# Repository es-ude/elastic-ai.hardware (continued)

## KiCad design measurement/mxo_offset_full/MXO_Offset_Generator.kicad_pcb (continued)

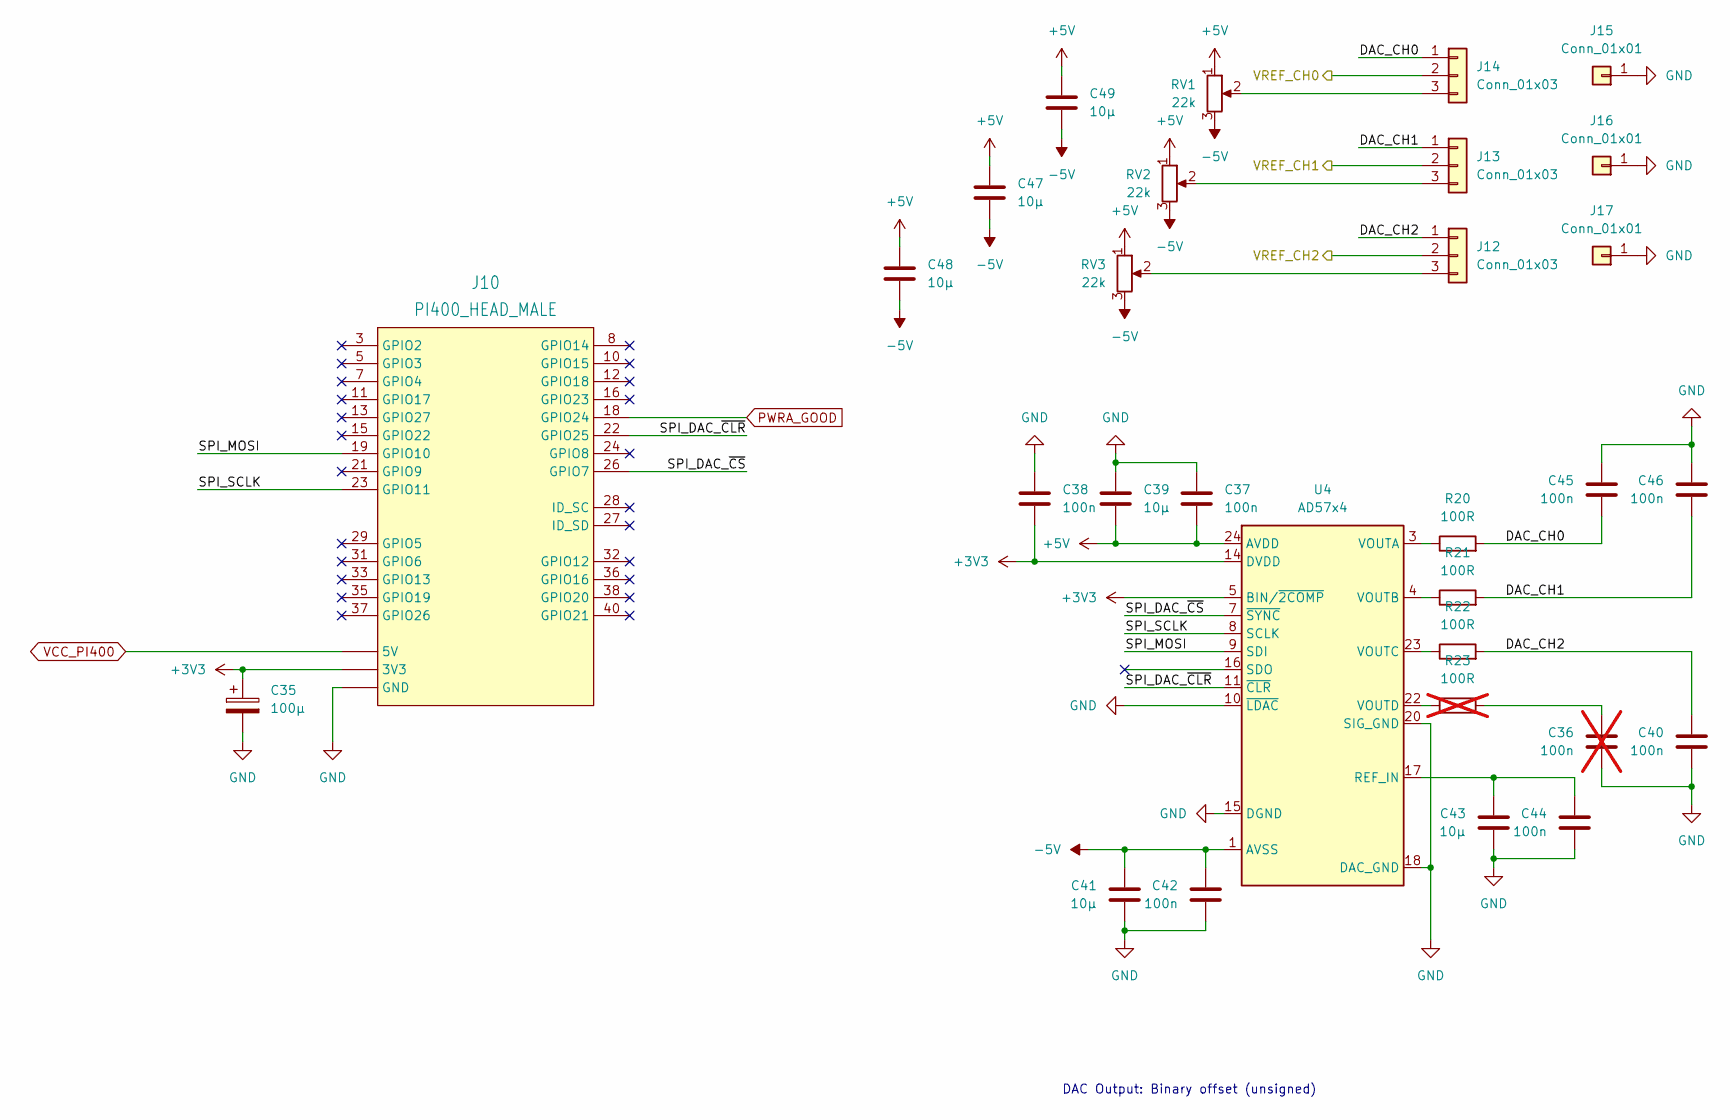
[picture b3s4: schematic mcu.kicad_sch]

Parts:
C35: 100µ; CP_Elec_4x3
C36: 100n; C_0603_1608Metric; not fitted
C37, C38, C40, C42, C44, C45, C46: 100n; C_0603_1608Metric
C39, C41, C43, C47, C48, C49: 10µ; C_0805_2012Metric
J10: PI400_HEAD_MALE; rpi400_header
J12, J13, J14: Conn_01x03; PinHeader_1x03_P2.54mm_Vertical
J15, J16, J17: Conn_01x01; PinHeader_1x01_P2.54mm_Vertical
R20, R21, R22: 100R; R_0603_1608Metric
R23: 100R; R_0603_1608Metric; not fitted
RV1, RV2, RV3: 22k; Potentiometer_Vishay_T73YP_Vertical
U4: AD57x4; TSSOP-24-1EP_4.4x7.8mm_P0.65mm_EP3.2x5mm

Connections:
+3V3: C35.1, C38.2, J10.1 (3V3), J10.17 (3V3), U4.5 (BIN/~2COMP), U4.14 (DVDD); also elsewhere on the board
+5V: C37.2, C39.2, C47.1, C48.1, C49.1, RV1.1, RV2.1, RV3.1, U4.24 (AVDD); also elsewhere on the board
-5V: C41.1, C42.1, C47.2, C48.2, C49.2, RV1.3, RV2.3, RV3.3, U4.1 (AVSS), U4.25 (AVSS_EXP); also elsewhere on the board
/Control-Unit/DAC_CH0: C45.2, J14.1, R20.2
/Control-Unit/DAC_CH1: C46.2, J13.1, R21.2
/Control-Unit/DAC_CH2: C40.1, J12.1, R22.2
/Control-Unit/SPI_DAC_~CLR: J10.22 (GPIO25), U4.11 (~CLR)
/Control-Unit/SPI_DAC_~CS: J10.26 (GPIO7), U4.7 (~SYNC)
/Control-Unit/SPI_MOSI: J10.19 (GPIO10), U4.9 (SDI)
/Control-Unit/SPI_SCLK: J10.23 (GPIO11), U4.8 (SCLK)
/Control-Unit/VREF_CH0: J14.2; also elsewhere on the board
/Control-Unit/VREF_CH1: J13.2; also elsewhere on the board
/Control-Unit/VREF_CH2: J12.2; also elsewhere on the board
GND: C35.2, C36.2, C37.1, C38.1, C39.1, C40.2, C41.2, C42.2, C43.2, C44.2, C45.1, C46.1, J10.6 (GND), J10.9 (GND), J10.14 (GND), J10.20 (GND), J10.25 (GND), J10.30 (GND), J10.34 (GND), J10.39 (GND), J15.1, J16.1, J17.1, U4.10 (~LDAC), U4.15 (DGND), U4.18 (DAC_GND), U4.19 (DAC_GND), U4.20 (SIG_GND), U4.21 (SIG_GND); also elsewhere on the board
unnamed: C36.1, R23.2
unnamed: J12.3, RV3.2
unnamed: J13.3, RV2.2
unnamed: J14.3, RV1.2
unnamed: C43.1, C44.1, U4.17 (REF_IN)
unnamed: R20.1, U4.3 (VOUTA)
unnamed: R21.1, U4.4 (VOUTB)
unnamed: R22.1, U4.23 (VOUTC)
unnamed: R23.1, U4.22 (VOUTD)
PWRA_GOOD: J10.18 (GPIO24); also elsewhere on the board
VCC_PI400: J10.2 (5V), J10.4 (5V); also elsewhere on the board

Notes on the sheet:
DAC Output: Binary offset (unsigned)

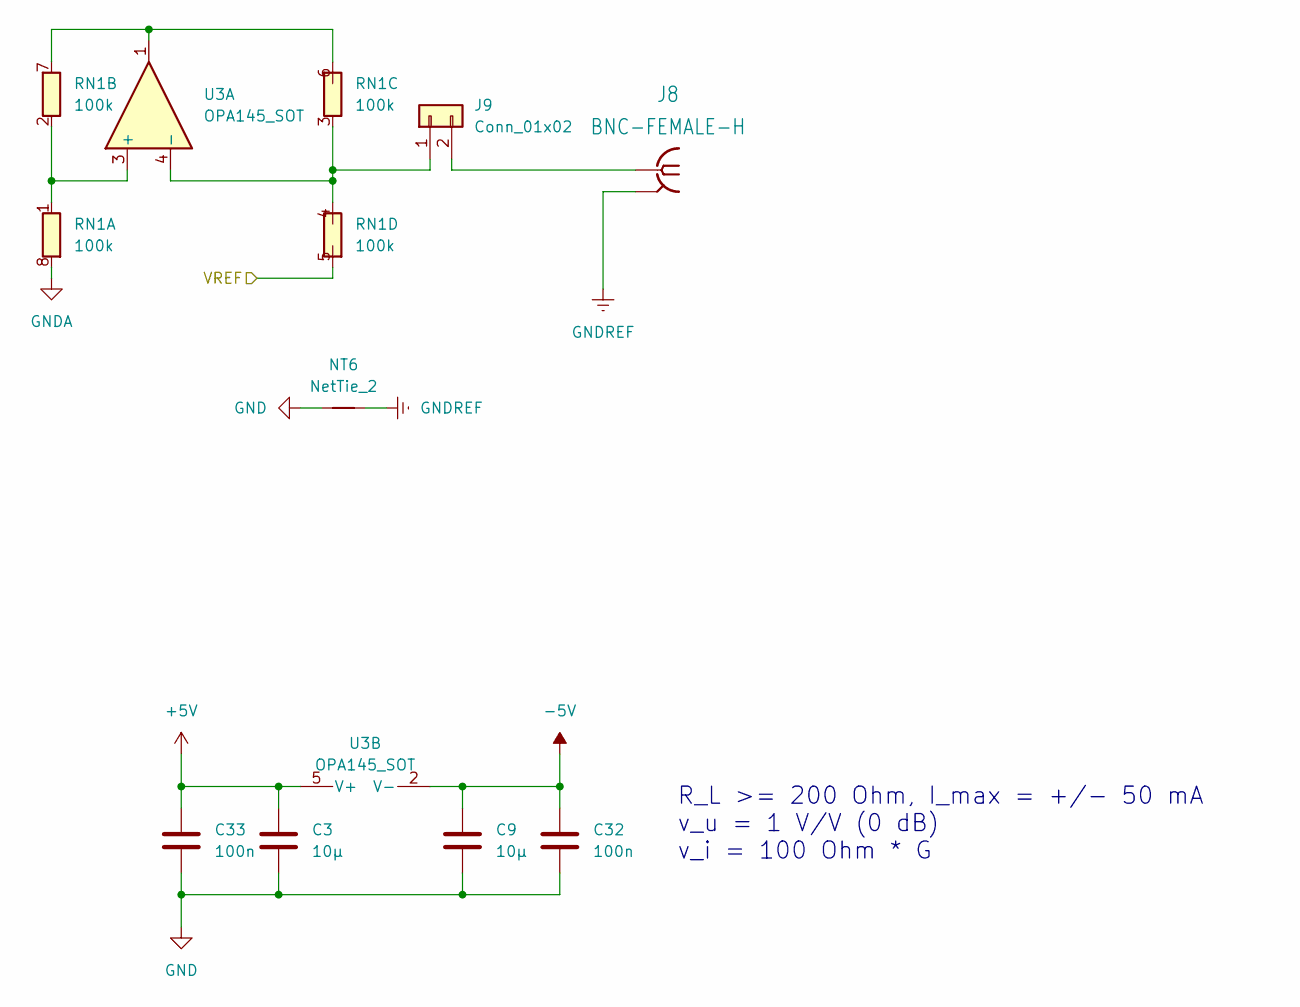
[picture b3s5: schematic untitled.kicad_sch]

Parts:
C3, C9: 10µ; C_0805_2012Metric
C32, C33: 100n; C_0603_1608Metric
J8: BNC-FEMALE-H; BNC-MALE-H
J9: Conn_01x02; PinHeader_1x02_P2.54mm_Vertical
NT6: NetTie_2; NetTie-2_SMD_Pad0.5mm
RN1: 100k; RESCAXE80P320X160X70-8N
U3: OPA145_SOT; SOT-23-5_HandSoldering

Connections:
+5V: C3.1, C33.1, U3.5 (V+); also elsewhere on the board
-5V: C9.1, C32.1, U3.2 (V-); also elsewhere on the board
/Control-Unit/VREF_CH2: RN1.5 (R4.2); also elsewhere on the board
GND: C3.2, C9.2, C32.2, C33.2, NT6.1; also elsewhere on the board
GNDA: RN1.8 (R1.2)
GNDREF: J8.2 (GND), NT6.2; also elsewhere on the board
unnamed: J8.1 (SIG), J9.2
unnamed: J9.1, RN1.3 (R3.1), RN1.4 (R4.1), U3.4 (-)
unnamed: RN1.1 (R1.1), RN1.2 (R2.1), U3.3 (+)
unnamed: RN1.6 (R3.2), RN1.7 (R2.2), U3.1

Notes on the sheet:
R_L >= 200 Ohm, I_max = +/- 50 mA v_u = 1 V/V (0 dB) v_i = 100 Ohm * G

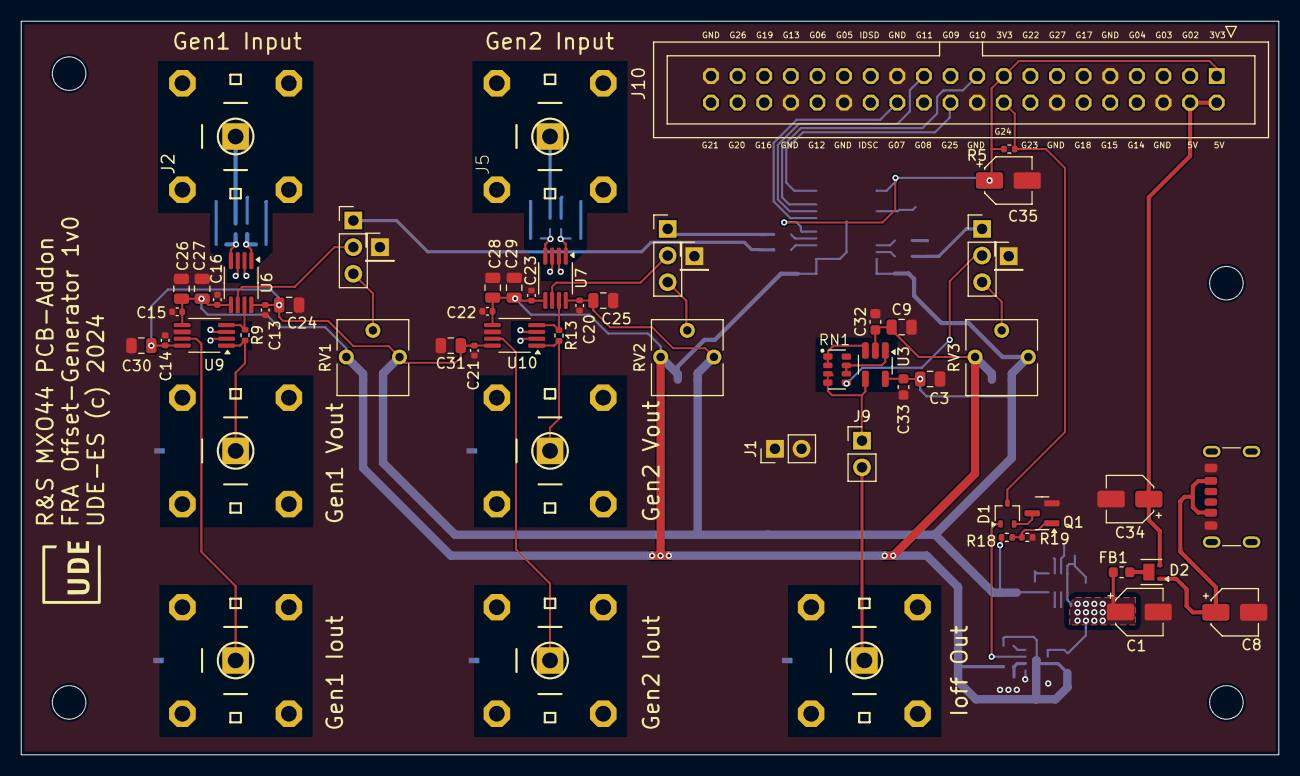
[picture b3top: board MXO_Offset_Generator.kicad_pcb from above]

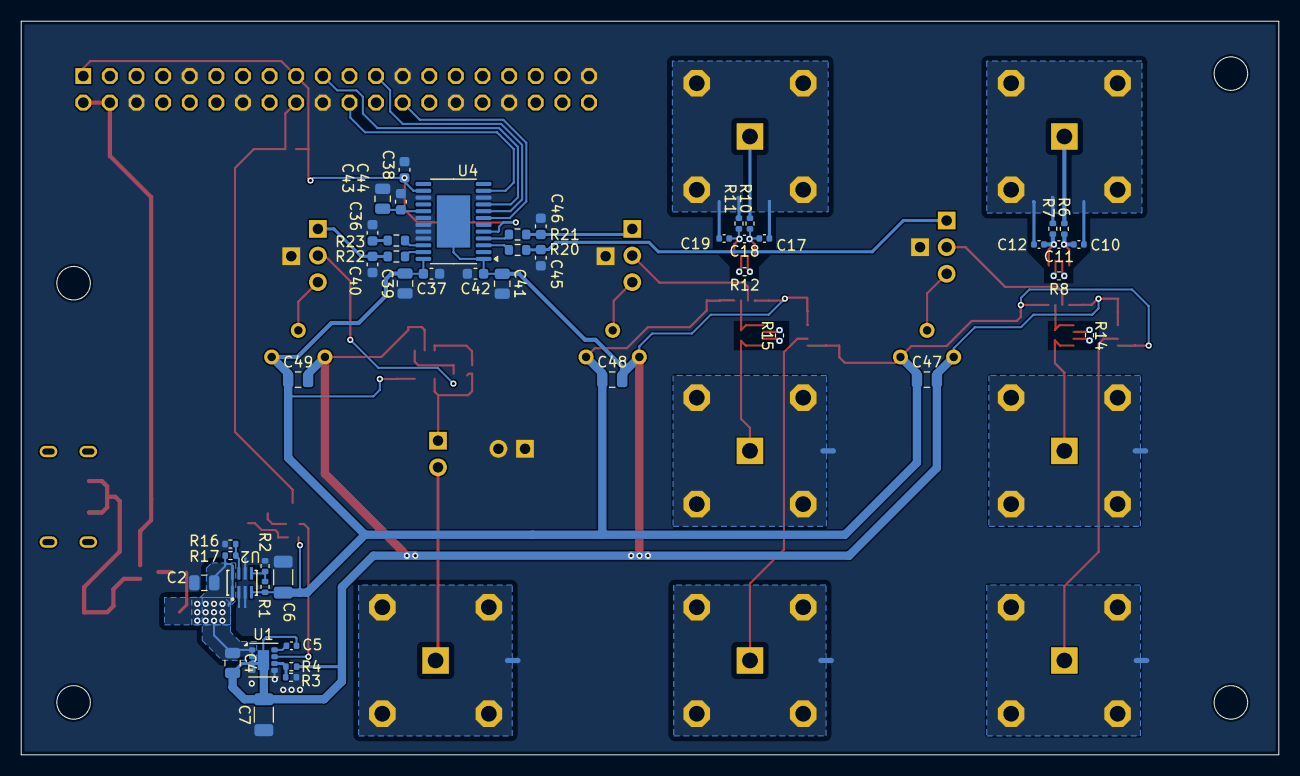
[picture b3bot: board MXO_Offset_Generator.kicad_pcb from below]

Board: 2 copper layers, 120.0 x 70.0 mm, 114 parts (51 on the bottom side), 60 nets.

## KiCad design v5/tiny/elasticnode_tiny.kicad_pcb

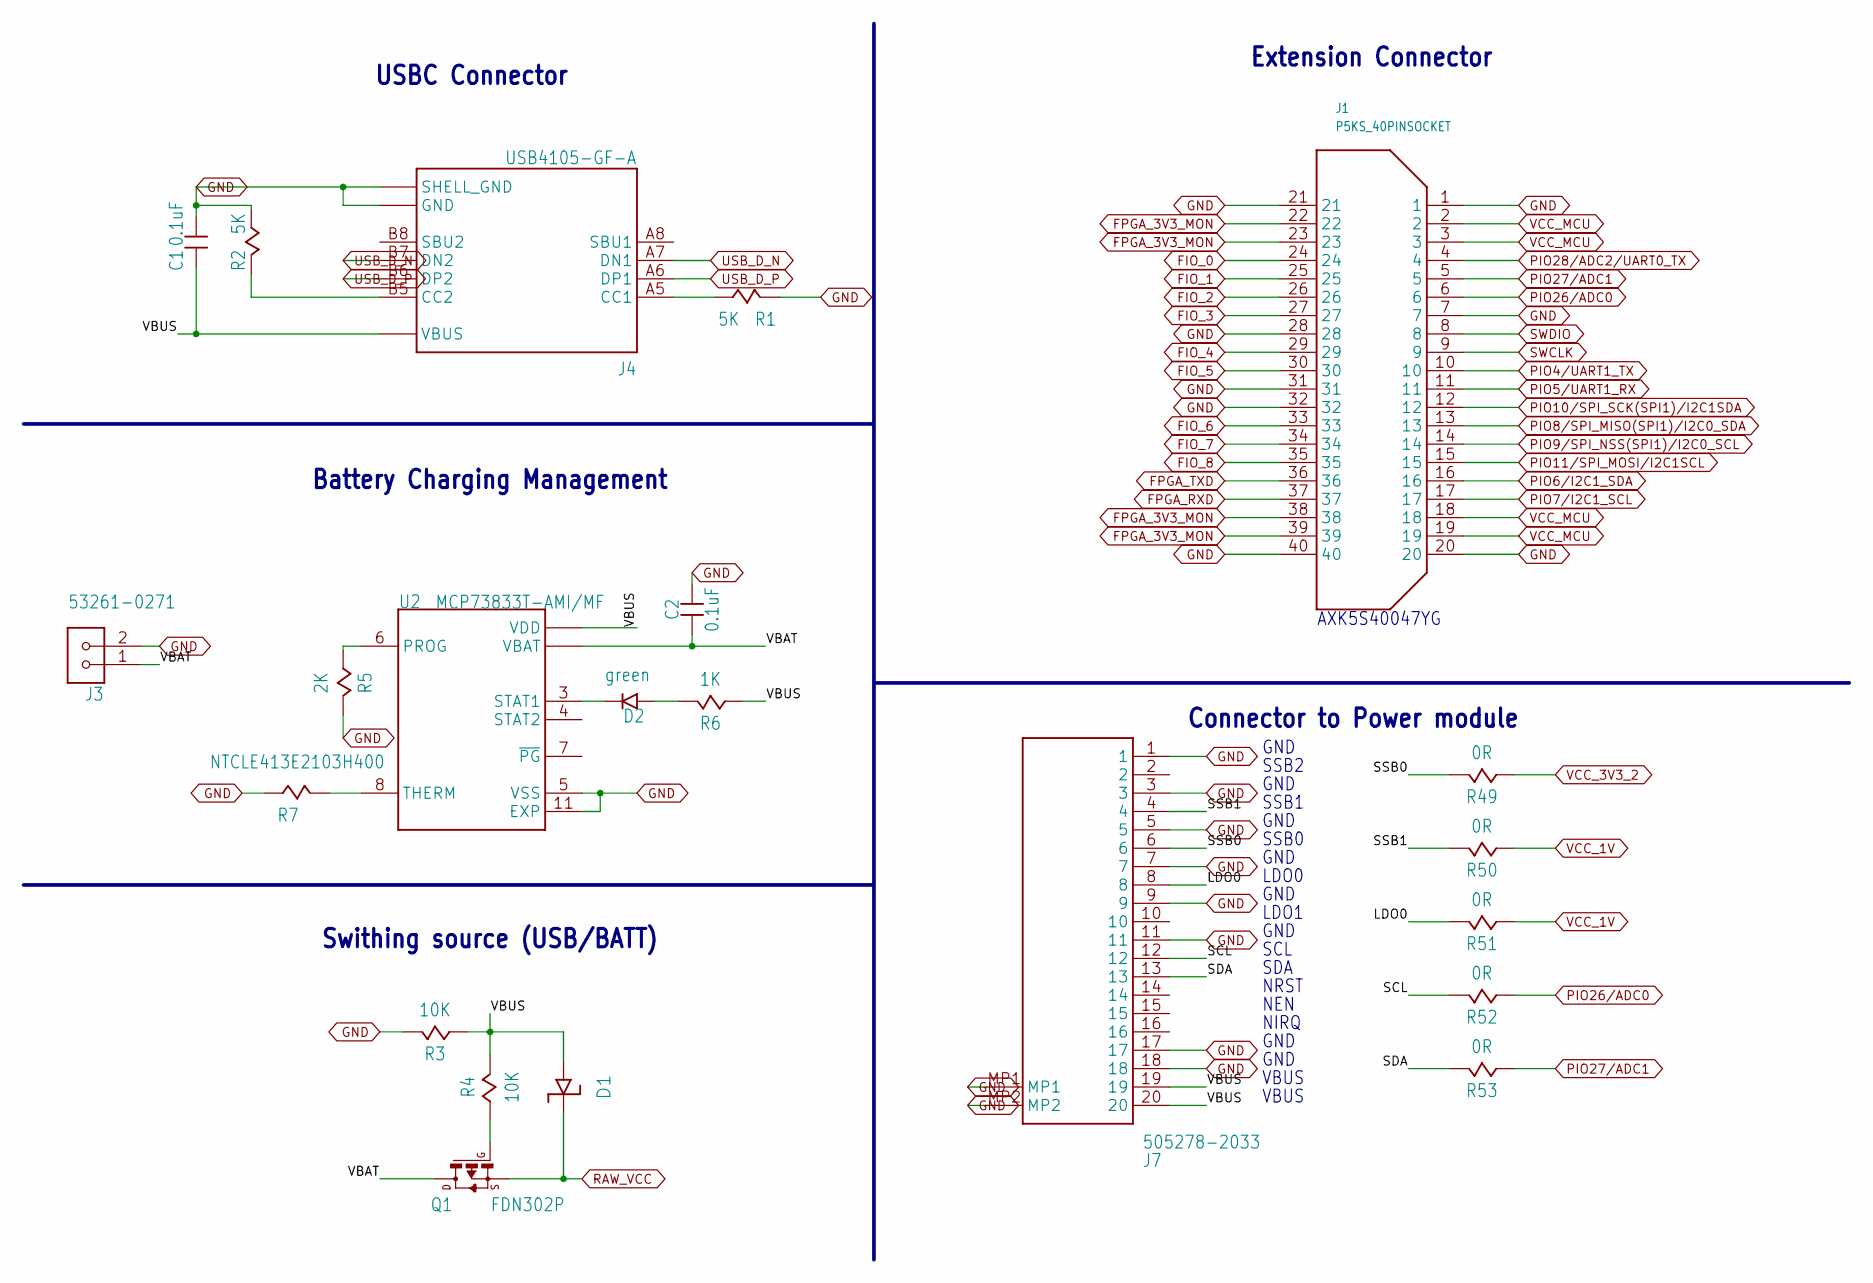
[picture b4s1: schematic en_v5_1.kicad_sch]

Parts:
C1: 0.1uF; 0402
C2: 0.1uF; 0805
D1: DIODEB5817W; SOD-123
D2: green; 0402
J1: P5KS_40PINSOCKET; P5KS_40PIN_SOCKET
J3: 53261-0271; MOLEX_53261-0271
J4: USB4105-GF-A; GCT_USB4105-GF-A
J7: 505278-2033; 5052782033
Q1: FDN302P; SSOT-3
R1, R2: 5K; 0402
R3, R4: 10K; 0402
R5: 2K; 0402
R6: 1K; 0402
R7: NTCLE413E2103H400; THT_2
R49, R50, R51, R52, R53: 0R; 0402
U2: MCP73833T-AMI/MF; DFN-10(3X3X0.9)

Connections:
FIO_0: J1.24; also elsewhere on the board
FIO_1: J1.25; also elsewhere on the board
FIO_2: J1.26; also elsewhere on the board
FIO_3: J1.27; also elsewhere on the board
FIO_4: J1.29; also elsewhere on the board
FIO_5: J1.30; also elsewhere on the board
FIO_6: J1.33; also elsewhere on the board
FIO_7: J1.34; also elsewhere on the board
FIO_8: J1.35; also elsewhere on the board
FPGA_3V3_MON: J1.22, J1.23, J1.38, J1.39; also elsewhere on the board
FPGA_RXD: J1.37; also elsewhere on the board
FPGA_TXD: J1.36; also elsewhere on the board
GND: C1.1, C2.2, J1.1, J1.7, J1.20, J1.21, J1.28, J1.31, J1.32, J1.40, J3.2, J4.A1_B12 (GND), J4.B1_A12 (GND), J4.S1 (SHELL_GND), J4.S2 (SHELL_GND), J4.S3 (SHELL_GND), J4.S4 (SHELL_GND), J7.1, J7.3, J7.5, J7.7, J7.9, J7.11, J7.17, J7.18, J7.MP1, J7.MP2, R1.2, R2.1, R3.2, R5.2, R7.P$1 (1), U2.5 (VSS), U2.11 (EXP); also elsewhere on the board
LDO0: J7.8, R51.2
unnamed: R7.P$2 (2), U2.8 (THERM)
unnamed: R5.1, U2.6 (PROG)
unnamed: Q1.1 (G), R4.1
unnamed: D2.2, U2.3 (STAT1)
unnamed: D2.1, R6.2
unnamed: J4.B5 (CC2), R2.2
unnamed: J4.A5 (CC1), R1.1
PIO4/UART1_TX: J1.10; also elsewhere on the board
PIO5/UART1_RX: J1.11; also elsewhere on the board
PIO6/I2C1_SDA: J1.16; also elsewhere on the board
PIO7/I2C1_SCL: J1.17; also elsewhere on the board
PIO8/SPI_MISO(SPI1)/I2C0_SDA: J1.13; also elsewhere on the board
PIO9/SPI_NSS(SPI1)/I2C0_SCL: J1.14; also elsewhere on the board
PIO10/SPI_SCK(SPI1)/I2C1SDA: J1.12; also elsewhere on the board
PIO11/SPI_MOSI/I2C1SCL: J1.15; also elsewhere on the board
PIO26/ADC0: J1.6, R52.1; also elsewhere on the board
PIO27/ADC1: J1.5, R53.1; also elsewhere on the board
PIO28/ADC2/UART0_TX: J1.4; also elsewhere on the board
RAW_VCC: D1.1 (C), Q1.2 (S); also elsewhere on the board
SCL: J7.12, R52.2
SDA: J7.13, R53.2
SSB0: J7.6, R49.2
SSB1: J7.4, R50.2
SWCLK: J1.9; also elsewhere on the board
SWDIO: J1.8; also elsewhere on the board
USB_D_N: J4.A7 (DN1), J4.B7 (DN2); also elsewhere on the board
USB_D_P: J4.A6 (DP1), J4.B6 (DP2); also elsewhere on the board
VBAT: C2.1, J3.1, Q1.3 (D), U2.9 (VBAT), U2.10 (VBAT)
VBUS: C1.2, D1.2 (A), J4.A4_B9 (VBUS), J4.B4_A9 (VBUS), J7.19, J7.20, R3.1, R4.2, R6.1, U2.1 (VDD), U2.2 (VDD)
VCC_1V: R50.1, R51.1; also elsewhere on the board
VCC_3V3_2: R49.1; also elsewhere on the board
VCC_MCU: J1.2, J1.3, J1.18, J1.19; also elsewhere on the board

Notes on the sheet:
AXK5S40047YG
GND
Swithing source (USB/BATT)
Extension Connector
VBUS
Battery Charging Management
NRST
SSB2
LDO1
SSB1
USBC Connector
Connector to Power module
SDA
SSB0
NEN
SCL
LDO0
NIRQ

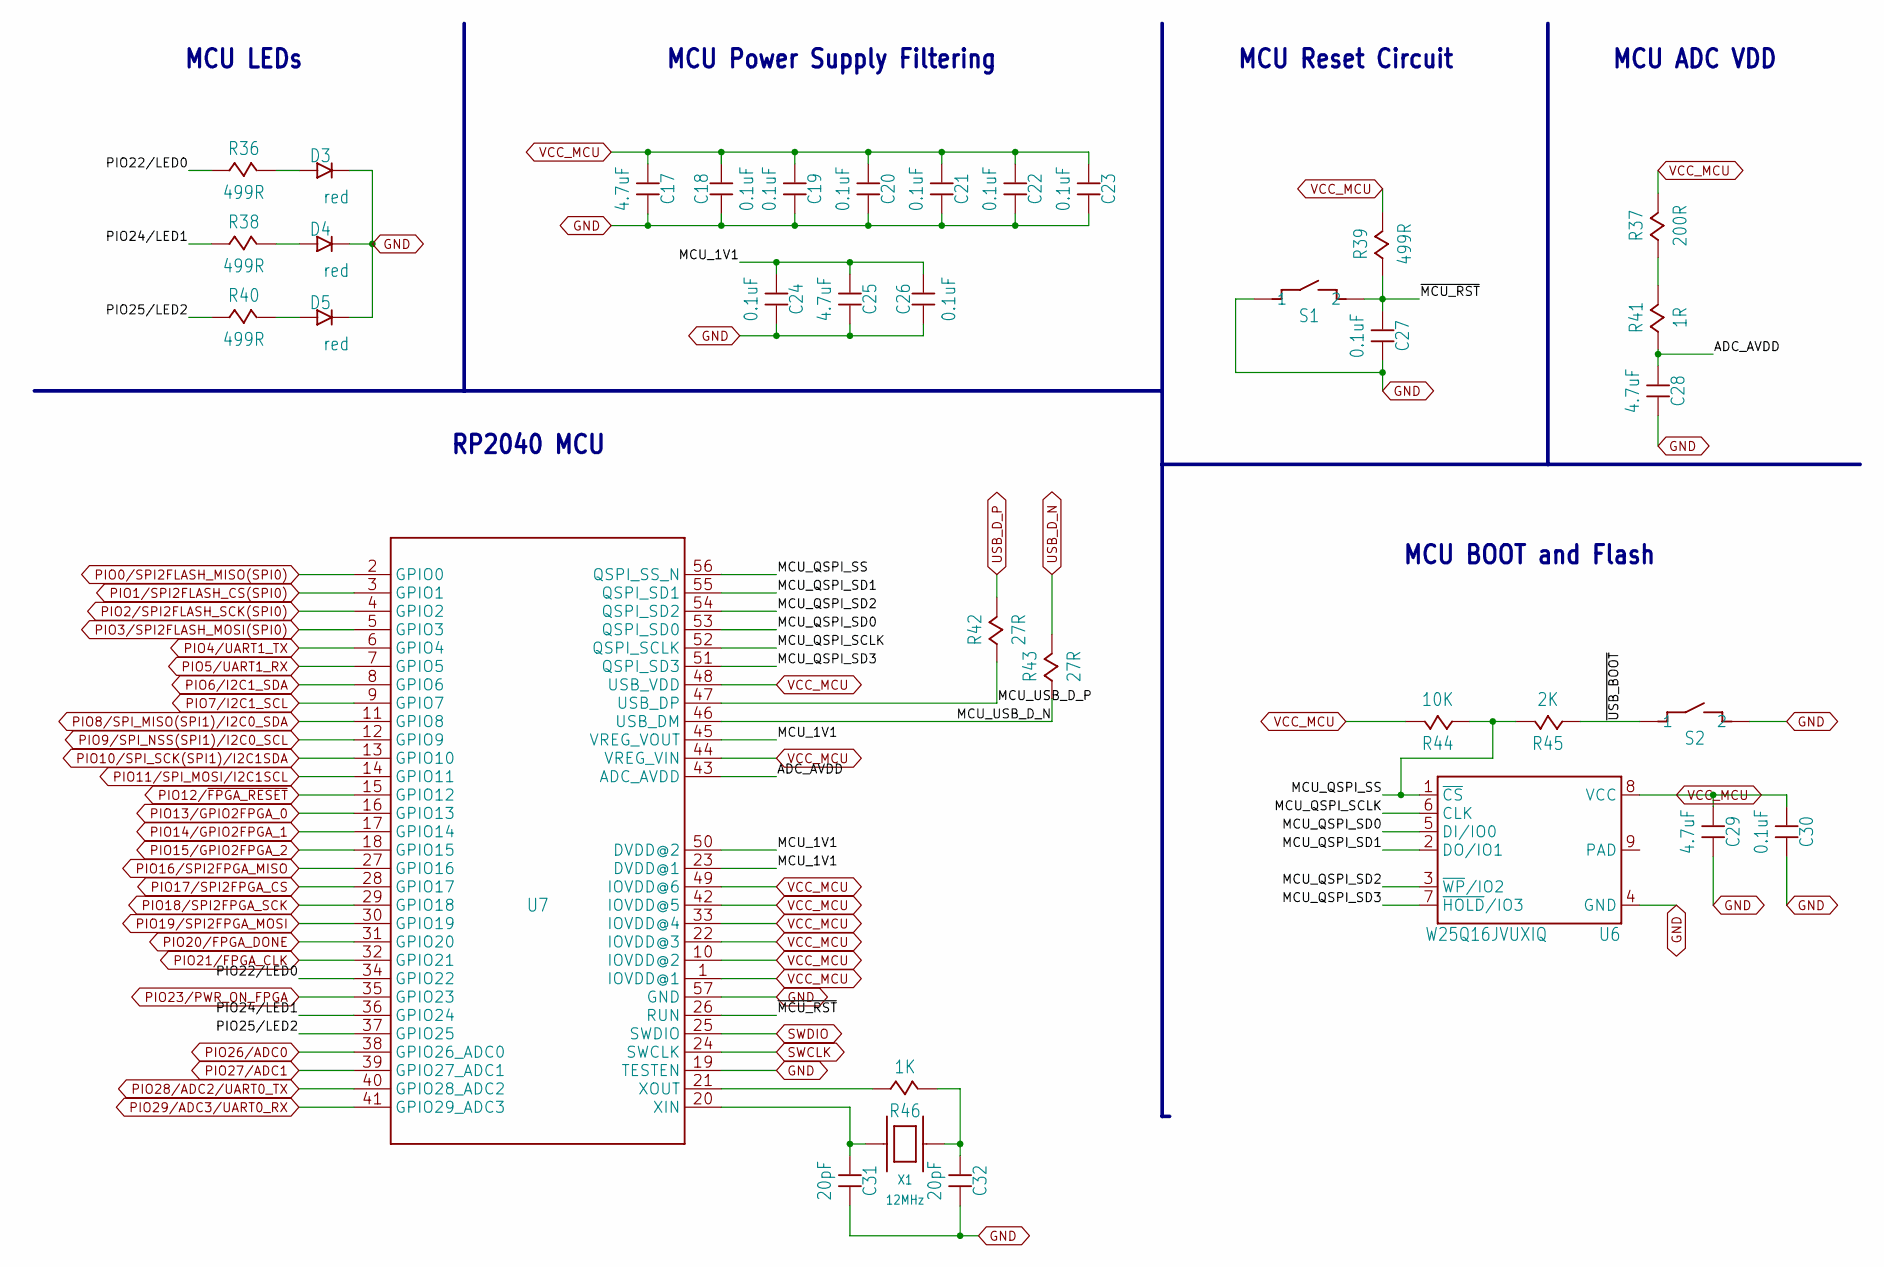
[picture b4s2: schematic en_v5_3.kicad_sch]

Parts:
C17, C25, C28, C29: 4.7uF; CAPC1608-0603
C18, C19, C20, C21, C22, C23, C24, C26, C27, C30: 0.1uF; 0402
C31, C32: 20pF; 0402
D3, D4, D5: red; 0402
R36, R38, R39, R40: 499R; 0402
R37: 200R; 0402
R41: 1R; 0402
R42, R43: 27R; 0402
R44: 10K; 0402
R45: 2K; 0402
R46: 1K; 0402
S1, S2: TACTILE-SWITCH
U6: W25Q16JVUXIQ; USON8-2X3MM
U7: RP2040; QFN40P700X700X100-57T310N
X1: 12MHz; 3.2X2.5_OSC

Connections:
ADC_AVDD: C28.1, R41.1, U7.43 (ADC_AVDD)
ADC_VREF: R37.1, R41.2
GND: C17.2, C18.1, C19.2, C20.2, C21.2, C22.2, C23.2, C24.2, C25.2, C26.1, C27.2, C28.2, C29.2, C30.2, C31.2, C32.2, D3.2, D4.2, D5.2, S1.1, S1.2 (1), S2.3 (2), S2.4 (2), U6.4 (GND), U7.19 (TESTEN), U7.57 (GND); also elsewhere on the board
MCU_1V1: C24.1, C25.1, C26.2, U7.23 (DVDD@1), U7.45 (VREG_VOUT), U7.50 (DVDD@2)
MCU_QSPI_SCLK: U6.6 (CLK), U7.52 (QSPI_SCLK)
MCU_QSPI_SD0: U6.5 (DI/IO0), U7.53 (QSPI_SD0)
MCU_QSPI_SD1: U6.2 (DO/IO1), U7.55 (QSPI_SD1)
MCU_QSPI_SD2: U6.3 (~WP/IO2), U7.54 (QSPI_SD2)
MCU_QSPI_SD3: U6.7 (~HOLD/IO3), U7.51 (QSPI_SD3)
MCU_QSPI_SS: R44.1, R45.2, U6.1 (~CS), U7.56 (QSPI_SS_N)
MCU_USB_D_N: R43.1, U7.46 (USB_DM)
MCU_USB_D_P: R42.1, U7.47 (USB_DP)
unnamed: R46.1, U7.21 (XOUT)
unnamed: C32.1, R46.2, X1.3
unnamed: C31.1, U7.20 (XIN), X1.1
unnamed: D3.1, R36.2
unnamed: D4.1, R38.2
unnamed: D5.1, R40.2
PIO0/SPI2FLASH_MISO(SPI0): U7.2 (GPIO0); also elsewhere on the board
PIO1/SPI2FLASH_CS(SPI0): U7.3 (GPIO1); also elsewhere on the board
PIO2/SPI2FLASH_SCK(SPI0): U7.4 (GPIO2); also elsewhere on the board
PIO3/SPI2FLASH_MOSI(SPI0): U7.5 (GPIO3); also elsewhere on the board
PIO4/UART1_TX: U7.6 (GPIO4); also elsewhere on the board
PIO5/UART1_RX: U7.7 (GPIO5); also elsewhere on the board
PIO6/I2C1_SDA: U7.8 (GPIO6); also elsewhere on the board
PIO7/I2C1_SCL: U7.9 (GPIO7); also elsewhere on the board
PIO8/SPI_MISO(SPI1)/I2C0_SDA: U7.11 (GPIO8); also elsewhere on the board
PIO9/SPI_NSS(SPI1)/I2C0_SCL: U7.12 (GPIO9); also elsewhere on the board
PIO10/SPI_SCK(SPI1)/I2C1SDA: U7.13 (GPIO10); also elsewhere on the board
PIO11/SPI_MOSI/I2C1SCL: U7.14 (GPIO11); also elsewhere on the board
PIO12/~FPGA_RESET: U7.15 (GPIO12); also elsewhere on the board
PIO13/GPIO2FPGA_0: U7.16 (GPIO13); also elsewhere on the board
PIO14/GPIO2FPGA_1: U7.17 (GPIO14); also elsewhere on the board
PIO15/GPIO2FPGA_2: U7.18 (GPIO15); also elsewhere on the board
PIO16/SPI2FPGA_MISO: U7.27 (GPIO16); also elsewhere on the board
PIO17/SPI2FPGA_CS: U7.28 (GPIO17); also elsewhere on the board
PIO18/SPI2FPGA_SCK: U7.29 (GPIO18); also elsewhere on the board
PIO19/SPI2FPGA_MOSI: U7.30 (GPIO19); also elsewhere on the board
PIO20/FPGA_DONE: U7.31 (GPIO20); also elsewhere on the board
PIO21/FPGA_CLK: U7.32 (GPIO21); also elsewhere on the board
PIO22/LED0: R36.1, U7.34 (GPIO22)
PIO23/PWR_ON_FPGA: U7.35 (GPIO23); also elsewhere on the board
PIO24/LED1: R38.1, U7.36 (GPIO24)
PIO25/LED2: R40.1, U7.37 (GPIO25)
PIO26/ADC0: U7.38 (GPIO26_ADC0); also elsewhere on the board
PIO27/ADC1: U7.39 (GPIO27_ADC1); also elsewhere on the board
PIO28/ADC2/UART0_TX: U7.40 (GPIO28_ADC2); also elsewhere on the board
PIO29/ADC3/UART0_RX: U7.41 (GPIO29_ADC3); also elsewhere on the board
SWCLK: U7.24 (SWCLK); also elsewhere on the board
SWDIO: U7.25 (SWDIO); also elsewhere on the board
USB_D_N: R43.2; also elsewhere on the board
USB_D_P: R42.2; also elsewhere on the board
VCC_MCU: C17.1, C18.2, C19.1, C20.1, C21.1, C22.1, C23.1, C29.1, C30.1, R37.2, R39.2, R44.2, U6.8 (VCC), U7.1 (IOVDD@1), U7.10 (IOVDD@2), U7.22 (IOVDD@3), U7.33 (IOVDD@4), U7.42 (IOVDD@5), U7.44 (VREG_VIN), U7.48 (USB_VDD), U7.49 (IOVDD@6); also elsewhere on the board
~MCU_RST: C27.1, R39.1, S1.3 (2), S1.4 (2), U7.26 (RUN)
~USB_BOOT: R45.1, S2.1, S2.2 (1)

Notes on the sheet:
MCU Power Supply Filtering
MCU BOOT and Flash
MCU Reset Circuit
RP2040 MCU
MCU LEDs
MCU ADC VDD

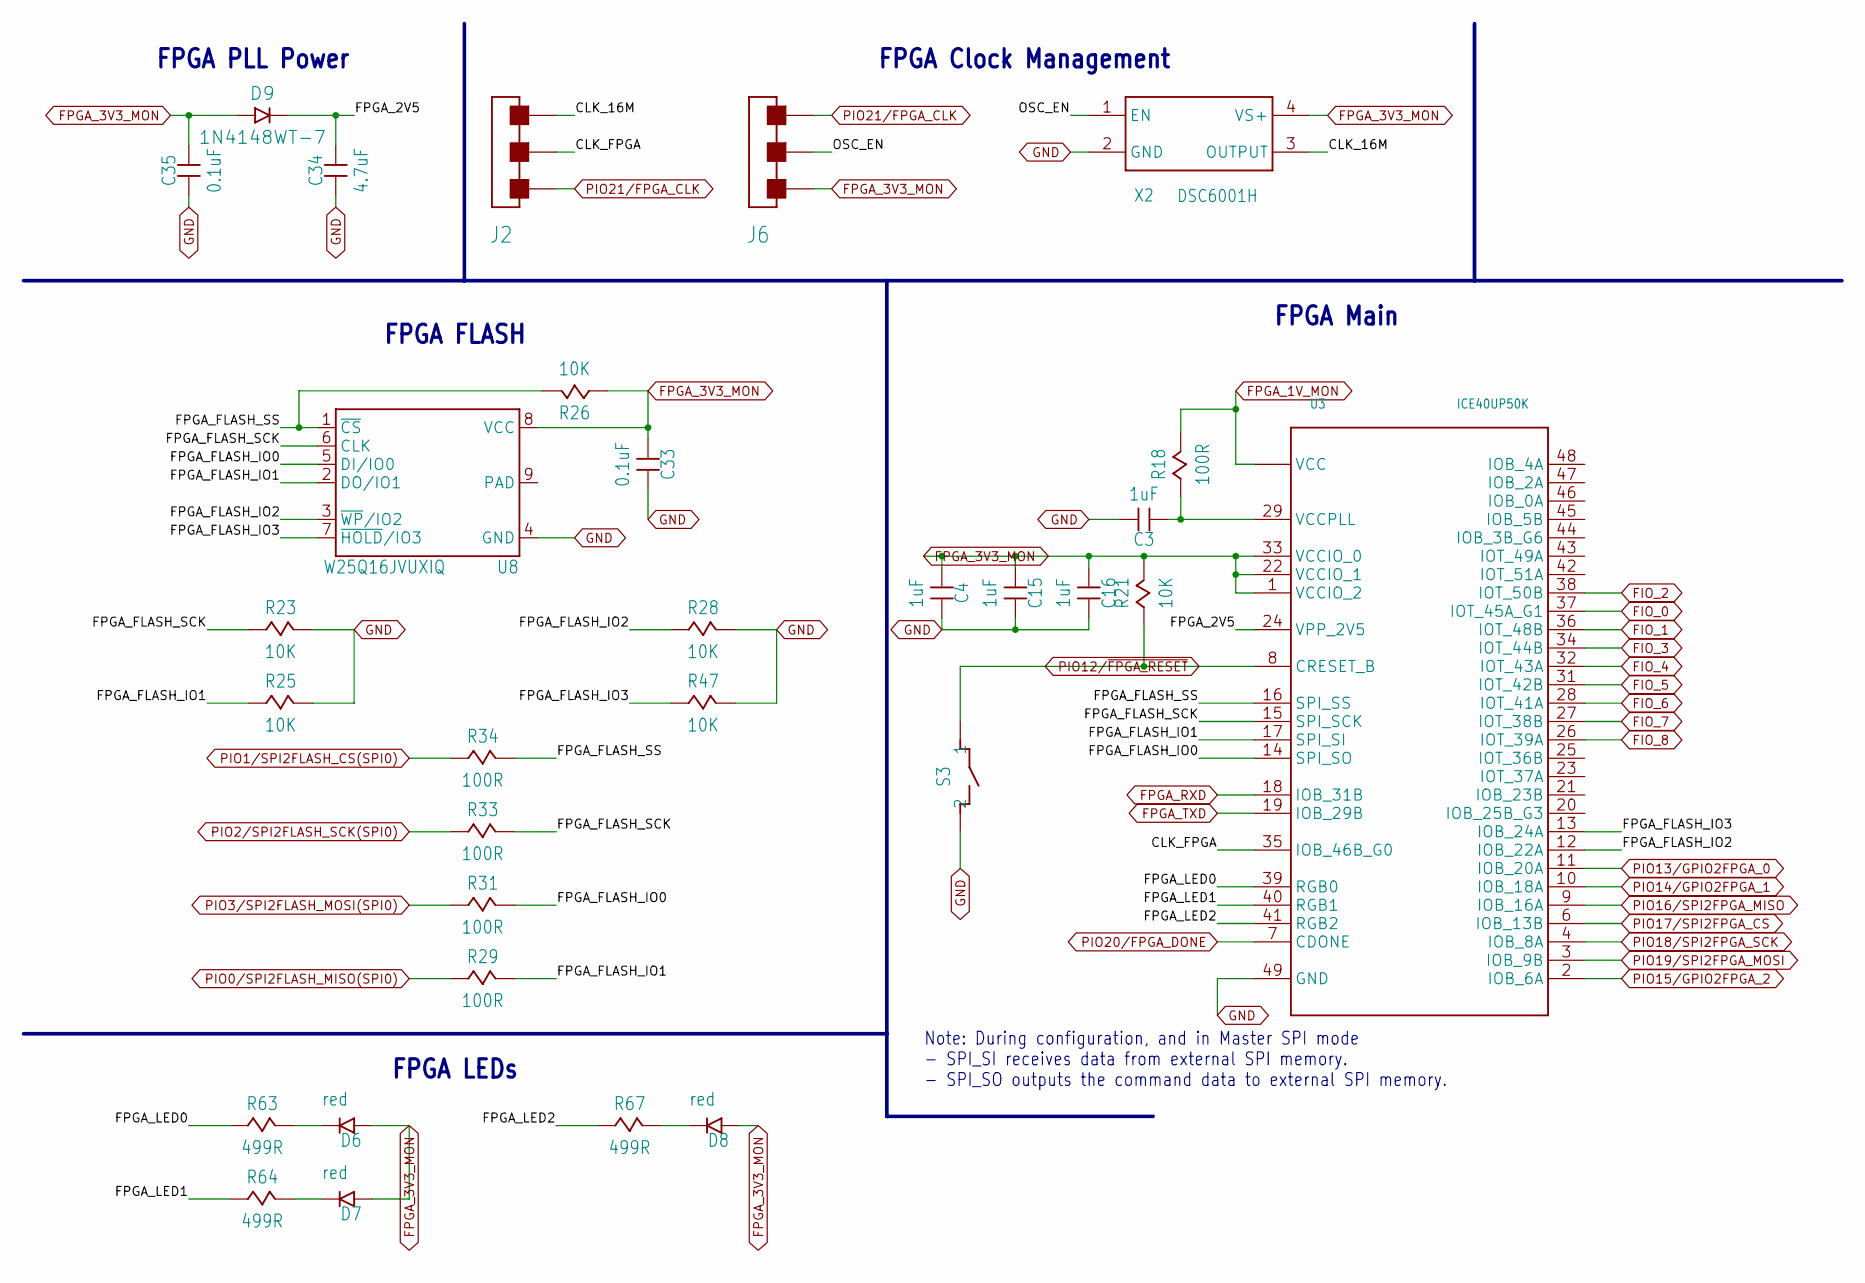
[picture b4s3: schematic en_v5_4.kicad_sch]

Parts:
C3, C4, C15, C16: 1uF; 0402
C33, C35: 0.1uF; 0402
C34: 4.7uF; 0402
D6, D7, D8: red; 0402
D9: 1N4148WT-7; SOD523
J2, J6: JUMPER3; JUMPER3_SMT_SMALL
R18, R29, R31, R33, R34: 100R; 0402
R21, R23, R25, R26, R28, R47: 10K; 0402
R63, R64, R67: 499R; 0402
S3: TACTILE-SWITCH
U3: ICE40UP50K; QFN48
U8: W25Q16JVUXIQ; USON8-2X3MM
X2: DSC6001H; 1.6X1.2_OSC

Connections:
CLK_16M: J2.R, X2.3 (OUTPUT)
CLK_FPGA: J2.C, U3.35 (IOB_46B_G0)
FIO_0: U3.37 (IOT_45A_G1); also elsewhere on the board
FIO_1: U3.36 (IOT_48B); also elsewhere on the board
FIO_2: U3.38 (IOT_50B); also elsewhere on the board
FIO_3: U3.34 (IOT_44B); also elsewhere on the board
FIO_4: U3.32 (IOT_43A); also elsewhere on the board
FIO_5: U3.31 (IOT_42B); also elsewhere on the board
FIO_6: U3.28 (IOT_41A); also elsewhere on the board
FIO_7: U3.27 (IOT_38B); also elsewhere on the board
FIO_8: U3.26 (IOT_39A); also elsewhere on the board
FPGA_1V_MON: R18.2, U3.5 (VCC), U3.30 (VCC); also elsewhere on the board
FPGA_2V5: C34.2, D9.C, U3.24 (VPP_2V5)
FPGA_3V3_MON: C4.1, C15.1, C16.1, C33.1, C35.2, D6.1, D7.1, D8.1, D9.A, J6.L, R21.2, R26.1, U3.1 (VCCIO_2), U3.22 (VCCIO_1), U3.33 (VCCIO_0), U8.8 (VCC), X2.4 (VS+); also elsewhere on the board
FPGA_FLASH_IO0: R31.2, U3.14 (SPI_SO), U8.5 (DI/IO0)
FPGA_FLASH_IO1: R25.1, R29.2, U3.17 (SPI_SI), U8.2 (DO/IO1)
FPGA_FLASH_IO2: R28.1, U3.12 (IOB_22A), U8.3 (~WP/IO2)
FPGA_FLASH_IO3: R47.1, U3.13 (IOB_24A), U8.7 (~HOLD/IO3)
FPGA_FLASH_SCK: R23.1, R33.2, U3.15 (SPI_SCK), U8.6 (CLK)
FPGA_FLASH_SS: R26.2, R34.2, U3.16 (SPI_SS), U8.1 (~CS)
FPGA_LED0: R63.1, U3.39 (RGB0)
FPGA_LED1: R64.1, U3.40 (RGB1)
FPGA_LED2: R67.1, U3.41 (RGB2)
FPGA_RXD: U3.18 (IOB_31B); also elsewhere on the board
FPGA_TXD: U3.19 (IOB_29B); also elsewhere on the board
GND: C3.2, C4.2, C15.2, C16.2, C33.2, C34.1, C35.1, R23.2, R25.2, R28.2, R47.2, S3.3 (2), S3.4 (2), U3.49 (GND), U8.4 (GND), X2.2 (GND); also elsewhere on the board
unnamed: C3.1, R18.1, U3.29 (VCCPLL)
unnamed: D6.2, R63.2
unnamed: D7.2, R64.2
unnamed: D8.2, R67.2
OSC_EN: J6.C, X2.1 (EN)
PIO0/SPI2FLASH_MISO(SPI0): R29.1; also elsewhere on the board
PIO1/SPI2FLASH_CS(SPI0): R34.1; also elsewhere on the board
PIO2/SPI2FLASH_SCK(SPI0): R33.1; also elsewhere on the board
PIO3/SPI2FLASH_MOSI(SPI0): R31.1; also elsewhere on the board
PIO12/~FPGA_RESET: R21.1, S3.1, S3.2 (1), U3.8 (CRESET_B); also elsewhere on the board
PIO13/GPIO2FPGA_0: U3.11 (IOB_20A); also elsewhere on the board
PIO14/GPIO2FPGA_1: U3.10 (IOB_18A); also elsewhere on the board
PIO15/GPIO2FPGA_2: U3.2 (IOB_6A); also elsewhere on the board
PIO16/SPI2FPGA_MISO: U3.9 (IOB_16A); also elsewhere on the board
PIO17/SPI2FPGA_CS: U3.6 (IOB_13B); also elsewhere on the board
PIO18/SPI2FPGA_SCK: U3.4 (IOB_8A); also elsewhere on the board
PIO19/SPI2FPGA_MOSI: U3.3 (IOB_9B); also elsewhere on the board
PIO20/FPGA_DONE: U3.7 (CDONE); also elsewhere on the board
PIO21/FPGA_CLK: J2.L, J6.R; also elsewhere on the board

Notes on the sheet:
FPGA Clock Management
FPGA LEDs
FPGA PLL Power
FPGA Main
FPGA FLASH
Note: During configuration, and in Master SPI mode - SPI_SI receives data from external SPI memory. - SPI_SO outputs the command data to external SPI memory.
